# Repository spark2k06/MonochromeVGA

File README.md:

# Description

MonochromeVGA is a product to enjoy the charm of those monochrome monitors of the time but in the current video systems, and more specifically in your PC monitor. Although it could be connected to any TV, monitor or video system that has VGA inputs.

Select green, amber or B&W as monochromatic color, among others. Change color to monochrome or vice versa easily.

https://hackaday.io/project/166041-monochromevga

Disclaimer:

It is recommended to use MonochromeVGA inside an shielded container, which can be as simple as a cardboard box lined with aluminium foil, because although unlikely, the VGA signal could interfere with other nearby devices and depending on the laws of your country, it could lead to fines.

In any case, use any hardware posted here at your own risk.

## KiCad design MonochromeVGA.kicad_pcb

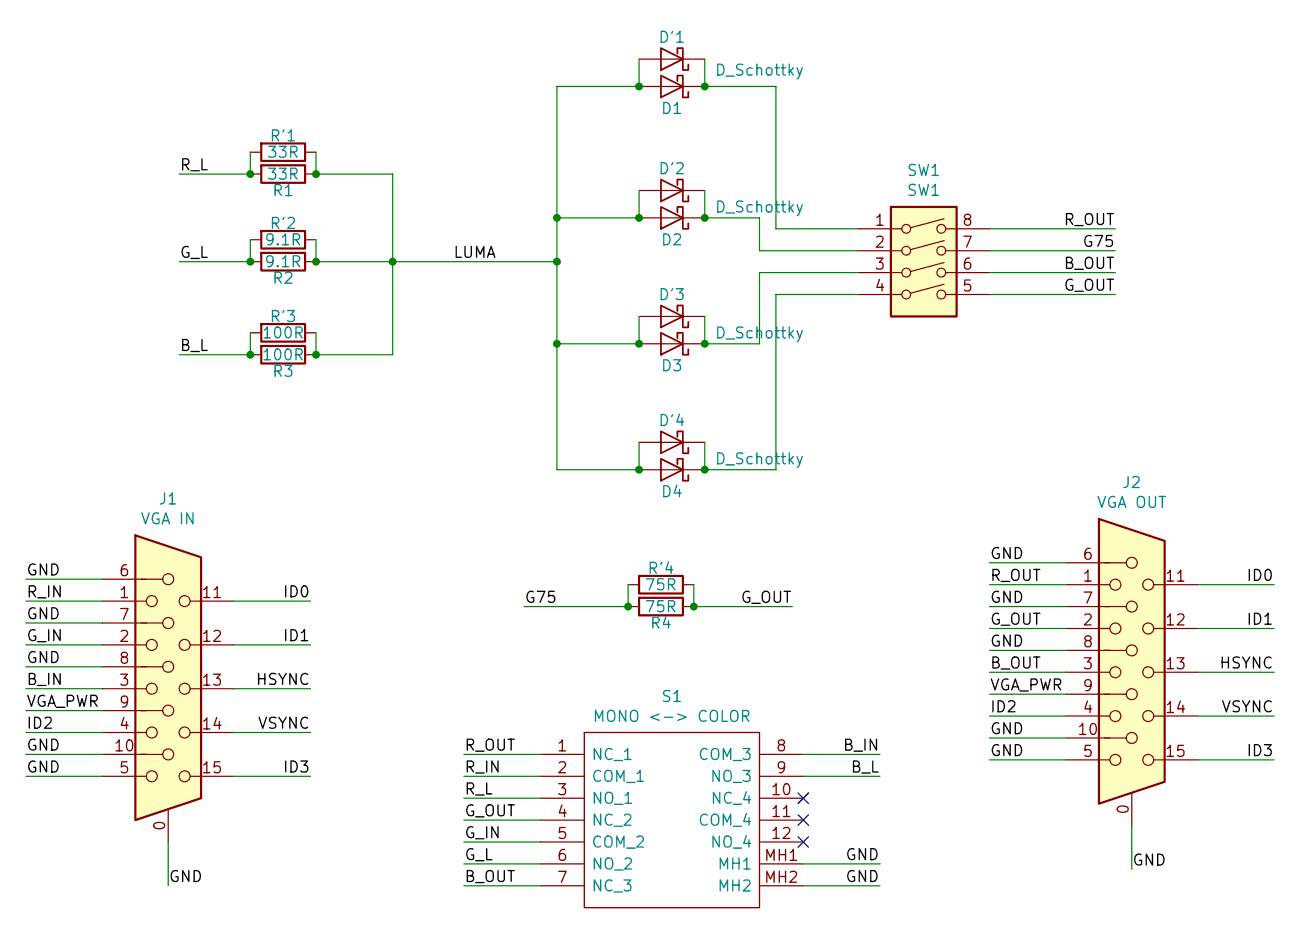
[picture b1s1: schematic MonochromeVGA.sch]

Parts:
D1, D2, D3, D4: D_Schottky; D_DO-35_SOD27_P7.62mm_Horizontal
D'1, D'2, D'3, D'4: D_SOD-123
J1: VGA IN; DSUB-15-HD_Female_Horizontal_P2.29x1.98mm_EdgePinOffset8.35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
J2: VGA OUT; DSUB-15-HD_Female_Horizontal_P2.29x1.98mm_EdgePinOffset8.35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
R1: 33R; R_Axial_DIN0204_L3.6mm_D1.6mm_P5.08mm_Horizontal
R2: 9.1R; R_Axial_DIN0204_L3.6mm_D1.6mm_P5.08mm_Horizontal
R3: 100R; R_Axial_DIN0204_L3.6mm_D1.6mm_P5.08mm_Horizontal
R4: 75R; R_Axial_DIN0204_L3.6mm_D1.6mm_P5.08mm_Horizontal
R'1: 33R; R_0603_1608Metric
R'2: 9.1R; R_0603_1608Metric
R'3: 100R; R_0603_1608Metric
R'4: 75R; R_0603_1608Metric
S1: MONO <-> COLOR; SW-SK-42D01-G; Mouser Part Number 612-EG4208A
SW1: SW1; SW_DIP_SPSTx04_Slide_9.78x12.34mm_W7.62mm_P2.54mm

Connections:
/B_IN: J1.3, S1.8 (COM_3)
/B_L: R3.2, R'3.2, S1.9 (NO_3)
/B_OUT: J2.3, S1.7 (NC_3), SW1.6
/G75: R4.2, R'4.2, SW1.7
/GND: J1.0, J1.5, J1.6, J1.7, J1.8, J1.10, J2.0, J2.5, J2.6, J2.7, J2.8, J2.10, S1.MH1, S1.MH2
/G_IN: J1.2, S1.5 (COM_2)
/G_L: R2.2, R'2.2, S1.6 (NO_2)
/G_OUT: J2.2, R4.1, R'4.1, S1.4 (NC_2), SW1.5
/HSYNC: J1.13, J2.13
/ID0: J1.11, J2.11
/ID1: J1.12, J2.12
/ID2: J1.4, J2.4
/ID3: J1.15, J2.15
/LUMA: D1.2 (A), D2.2 (A), D3.2 (A), D4.2 (A), D'1.2 (A), D'2.2 (A), D'3.2 (A), D'4.2 (A), R1.1, R2.1, R3.1, R'1.1, R'2.1, R'3.1
/R_IN: J1.1, S1.2 (COM_1)
/R_L: R1.2, R'1.2, S1.3 (NO_1)
/R_OUT: J2.1, S1.1 (NC_1), SW1.8
/VGA_PWR: J1.9, J2.9
/VSYNC: J1.14, J2.14
unnamed: D1.1 (K), D'1.1 (K), SW1.1
unnamed: D2.1 (K), D'2.1 (K), SW1.2
unnamed: D3.1 (K), D'3.1 (K), SW1.3
unnamed: D4.1 (K), D'4.1 (K), SW1.4

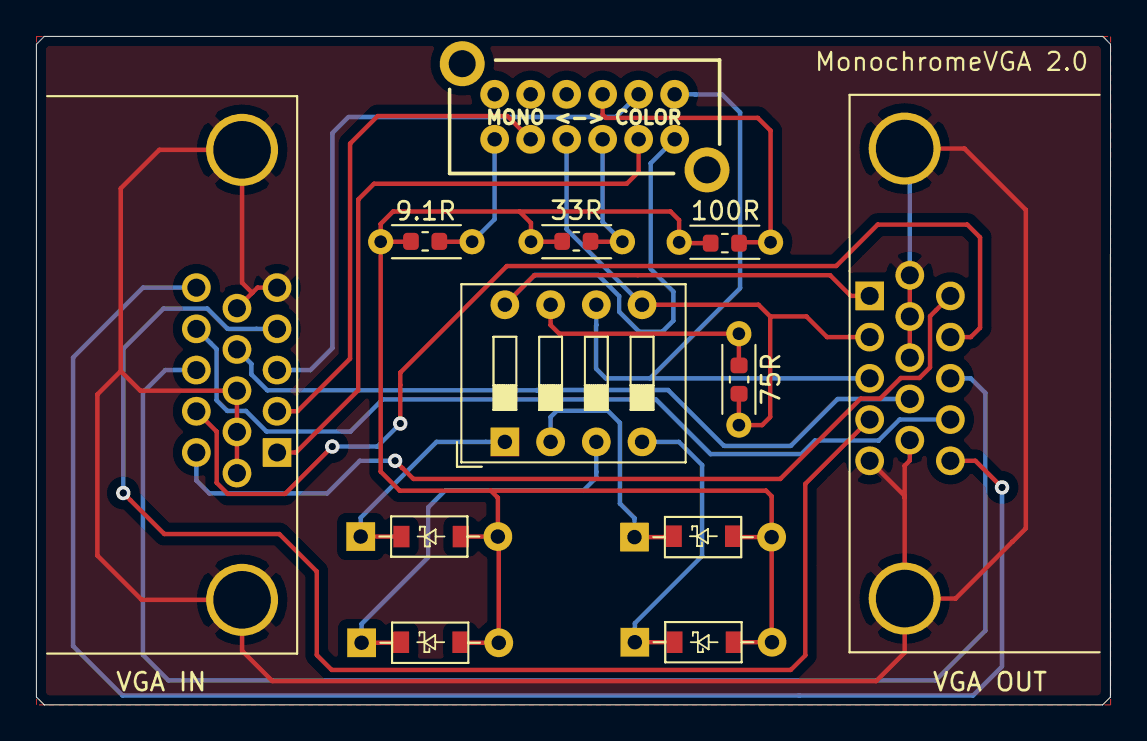
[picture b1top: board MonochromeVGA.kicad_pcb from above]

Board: 2 copper layers, 59.7 x 37.1 mm, 20 parts (0 on the bottom side), 23 nets.

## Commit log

2020-12-16 Version 2.0
    Changes from old revision
    The RGB resistors provided are 90% smaller in value, silkscreen indication has been fixed. The filtered output signal is brighter, it can be considered an improvement.
    The VGA input connector is now also female, to prioritize use in a case and more accessible to the user. However, a Mini Gender Changer is also offered, but this time male-male, to connect directly t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
    New PCB design with through hole technology and mixed SMD, for an assembly task adapted to the needs of each one.
2020-12-18 Update to License CERN, according to open hardware
2020-12-19 Update LICENSES
2020-12-21 Update licence to CERN-OHL-W
2022-05-26 3D Case
